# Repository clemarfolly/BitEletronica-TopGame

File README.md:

# A Bit Eletrônica e o Top Game

A Bit Eletrônica, fundada no Rio de Janeiro por Guilherme Ferramenta, criou o Top Game, o primeiro console de videogame brasileiro, lançado em dezembro de 1982. O console tinha um design diferenciado e era compatível com o sistema de TV PAL-M do Brasil. No entanto, ele utilizava um padrão próprio de cartuchos, devido ao receio de represálias da Atari. Apesar de boa aceitação inicial, a falta de capital e de publicidade, além da chegada de concorrentes maiores como a Philips e a Polyvox, levaram ao fim da Bit Eletrônica após a fabricação de cinco mil unidades. O Top Game tornou-se uma raridade entre colecionadores. Em 1984, a empresa lançou um adaptador para cartuchos do Atari 2600, mas isso não foi suficiente para salvar o negócio.

## Sobre essa reprodução

A reprodução do projeto foi realizada sem acesso físico à placa original, com base em fotos encontradas na internet. Para isso, utilizou-se os software Sprint Layout e o KiCad para desenhar o esquema e a placa de circuito impresso. A réplica ainda não foi produzida, e seu funcionamento não foi validado. Agradecemos às pessoas que disponibilizaram as fotos e o esquema original, permitindo que esse trabalho fosse possível.

### Datalhes das placas
A placa é dupla face, mesmo assim existem alguns jumpers. Esses jumpers foram roteados nas camadas internas de uma placa de 4 camadas. 

### Comparação com a placa original
Embora eu não tenha tido acesso físico à placa original, me esforcei para que a recriação ficasse o mais fiel possível. As imagens utilizadas como referência tinham baixa resolução e precisaram ter suas proporções ajustadas, além de estarem carregadas de componentes, o que complicou a reprodução das trilhas que passam por baixo deles.

## Créditos

### Recriação da Placa: 

Clemar Folly Jr.

https://x.com/clemarfolly/

### Fotos

Marcelo Savio

https://web.facebook.com/msavio.fb/posts/pfbid06LcW7Tc7TT6NtnfWvrCvcL87vY5sa6EqBfuqB7YxEga17TYGUfypFnMQQWhqyX86l

### Esquema

Alexandre Souza

http://www.tabalabs.com.br/esquemateca/$ESBREL/$pre-tratados/Top%20Game%20-%20Bit%20Eletronica.jpg

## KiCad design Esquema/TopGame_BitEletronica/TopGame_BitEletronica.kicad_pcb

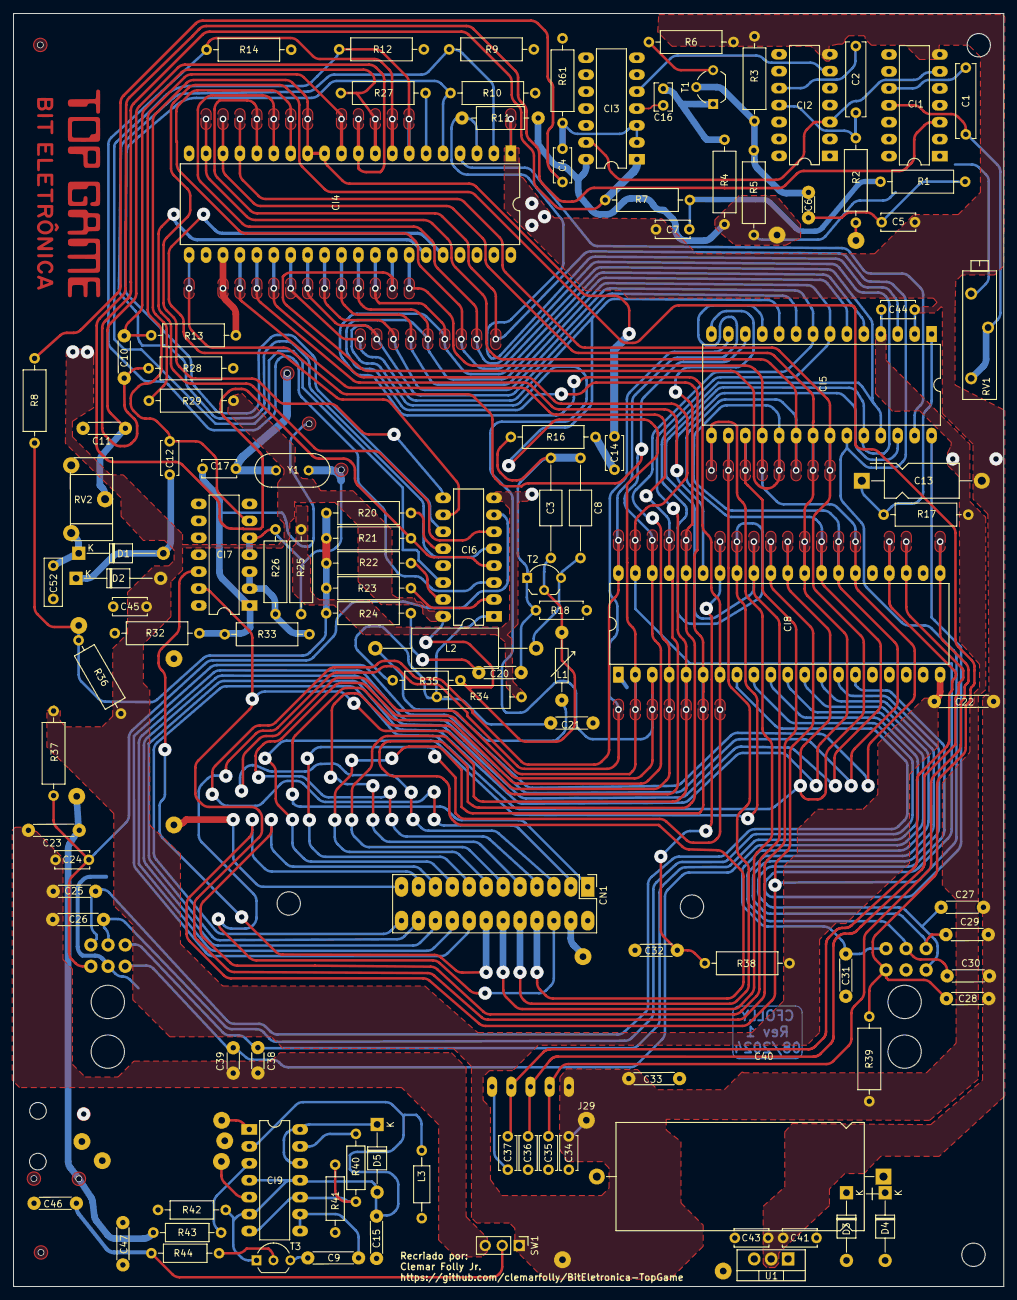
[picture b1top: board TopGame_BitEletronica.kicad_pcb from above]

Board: 4 copper layers, 148.5 x 190.9 mm, 144 parts (0 on the bottom side), 98 nets.

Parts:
C1, C2: C_Small; C_Rect_L11.0mm_W2.8mm_P10.00mm_MKT
C3, C8: 820p; C_Axial_L5.1mm_D3.1mm_P15.00mm_Horizontal
C4, C5, C7, C12, C17, C24, C34, C35, C36, C37, C41, C43, C45: C_Small; C_Disc_D5.0mm_W2.5mm_P5.00mm
C6, C38, C39: C_Small; C_Disc_D3.0mm_W1.6mm_P3.81mm
C9: 15p; C_Disc_D3.0mm_W1.6mm_P7.62mm
C10, C15, C20: 47p; C_Disc_D3.0mm_W1.6mm_P6.35mm
C11, C25, C27, C29, C30, C31, C46, C47: C_Small; C_Disc_D3.0mm_W1.6mm_P6.35mm
C13: 4.7uF/16V; CP_Axial_L11.0mm_D5.0mm_P18.00mm_Horizontal
C14: 100n; C_Disc_D5.0mm_W2.5mm_P5.00mm
C16: C_Small; C_Rect_L4.0mm_W2.5mm_P2.50mm
C21, C28: 220p; C_Disc_D3.0mm_W1.6mm_P6.35mm
C22: C_Mini; C_Disc_D3.0mm_W1.6mm_P8.89mm
C23, C26, C33: C_Small; C_Disc_D3.0mm_W1.6mm_P7.62mm
C32: C_Mini; C_Disc_D3.0mm_W1.6mm_P6.35mm
C40: CP_Small; CP_Axial_L37.0mm_D16.0mm_P43.00mm_Horizontal
C44: C_Mini; C_Disc_D5.0mm_W2.5mm_P5.00mm
C52: C_Small; C_Disc_D7.0mm_W2.5mm_P5.00mm
CI1, CI2: 74LS121; DIP-14_W7.62mm_LongPads
CI3: 4066; DIP-14_W7.62mm_LongPads
CI4: TIA; DIP-40_W15.24mm_LongPads
CI5: 6507; DIP-28_W15.24mm_LongPads
CI6: CD4050; DIP-16_W7.62mm_LongPads
CI7: 74LS04_SMALL; DIP-14_W7.62mm_LongPads
CI8: RIOT; DIP-40_W15.24mm_LongPads
CI9: LM3086; DIP-14_W7.62mm_LongPads
CN1: Conn_02x12_Counter_Clockwise; Atari2600_PCB_Edge_Connector_2x12_P2.54mm_5.08mm
D1, D2: D_ALT; D_T-1_P12.70mm_Horizontal
D3, D4, D5: D_ALT; D_T-1_P10.16mm_Horizontal
J3, J10: 6; Pin_2mm_Furo_1mm
J4, J11: 5; Pin_2mm_Furo_1mm
J6, J13: 7; Pin_2mm_Furo_1mm
J7, J14: 2; Pin_2mm_Furo_1mm
J8, J15: 3; Pin_2mm_Furo_1mm
J9, J16: 4; Pin_2mm_Furo_1mm
J17: +5V; Via Oval
J18: GND; Via Oval
J19: PB/C; Via Oval
J20: PAF; Via Oval
J21: SEL.; Via Oval
J22: +5V; Pad_3mm_furo_1mm
J23, J25, J26: GND; Pad_3mm_furo_1mm
J24: L4_3; Pad_3mm_furo_1mm
J27, J28, J29, J30, J31, J32, J33, J34: Pad_3mm_furo_1mm
L1: LTRIM; Indutor_Variavel_10.16mm
L2: L_Small; L_Axial_L12.8mm_D5.8mm_P24.13mm_Horizontal
L3: L; L_Axial_L5.3mm_D2.2mm_P10.16mm_Horizontal_Vishay_IM-1
R1, R2, R3, R4, R5, R6, R7, R8, R25, R26, R29, R32, R33, R36, R37, R38, R61: R; R_Axial_DIN0309_L9.0mm_D3.2mm_P12.70mm_Horizontal
R9, R10, R12, R14: 3k3; R_Axial_DIN0309_L9.0mm_D3.2mm_P12.70mm_Horizontal
R11: R; R_Axial_DIN0309_L9.0mm_D3.2mm_P11.43mm_Horizontal
R13, R24, R28: 1k; R_Axial_DIN0309_L9.0mm_D3.2mm_P12.70mm_Horizontal
R16: 18k; R_Axial_DIN0309_L9.0mm_D3.2mm_P12.70mm_Horizontal
R17, R21, R34, R39: 10k; R_Axial_DIN0309_L9.0mm_D3.2mm_P12.70mm_Horizontal
R18: 9k1; R_Axial_DIN0207_L6.3mm_D2.5mm_P7.62mm_Horizontal
R20: 24k; R_Axial_DIN0309_L9.0mm_D3.2mm_P12.70mm_Horizontal
R22: 12k; R_Axial_DIN0309_L9.0mm_D3.2mm_P12.70mm_Horizontal
R23: 47k; R_Axial_DIN0309_L9.0mm_D3.2mm_P12.70mm_Horizontal
R27: 680R; R_Axial_DIN0309_L9.0mm_D3.2mm_P12.70mm_Horizontal
R35: R; R_Axial_DIN0207_L6.3mm_D2.5mm_P10.16mm_Horizontal
R40: 1k5; R_Axial_DIN0207_L6.3mm_D2.5mm_P10.16mm_Horizontal
R41: 1k; R_Axial_DIN0207_L6.3mm_D2.5mm_P10.16mm_Horizontal
R42: 100R; R_Axial_DIN0207_L6.3mm_D2.5mm_P10.16mm_Horizontal
R43: 330R; R_Axial_DIN0207_L6.3mm_D2.5mm_P10.16mm_Horizontal
R44: 2k7; R_Axial_DIN0207_L6.3mm_D2.5mm_P10.16mm_Horizontal
RV1: R_POT_TRIM; Potentiometer_Bourns_3006P_Horizontal
RV2: R_POT_TRIM; Trimpot_14mm_Vertical
SW1: CHAVE CANAL; PinHeader_1x03_P2.54mm_Vertical
T1: NPN; TO-92_Wide
T2: MPS3563; TO-92_Invert_Wide
T3: MPS3906; TO-92_Inline_Wide
TP1, TP2: TestPoint; Pad_3mm_furo_1mm
U1: L7805; TO-220-3_Vertical
Y1: Crystal_Small; Crystal_HC49-U_Vertical

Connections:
+5V: C3.2, C22.1, C33.2, C34.1, C43.1, C44.1, C45.1, C47.1, CI1.14, CI2.14, CI3.14, CI4.20 (VCC), CI4.23 (CS1), CI5.4 (VCC), CI6.16, CI7.14 (VCC), CI8.20 (VDD), CN1.23, D2.2 (A), J17.1, J22.1, J28.1, J29.1, J30.1, J31.1, J32.1, J33.1, L1.1, R2.2, R4.2, R5.2, R9.1, R10.2, R11.1, R12.2, R13.2, R14.1, R17.2, R28.2, R29.1, R35.1, R36.2, R37.1, R38.1, R39.2, R42.1, RV1.3, SW1.1 (A), T2.2 (B), U1.3 (OUT)
+9V: C40.1, C41.1, D3.1 (K), D4.1 (K), U1.1 (IN)
D0: CI4.14 (D0), CI5.25 (D0), CI8.33 (D0), CN1.9
D1: CI4.15 (D1), CI5.24 (D1), CI8.32 (D1), CN1.10
GND: C5.2, C7.2, C11.2, C13.2, C21.1, C22.2, C23.2, C24.2, C25.2, C26.2, C27.2, C28.2, C29.2, C30.2, C31.2, C32.2, C33.1, C34.2, C35.2, C36.2, C37.2, C38.2, C39.2, C40.2, C41.2, C43.2, C44.2, C45.2, C46.2, C47.2, C52.2, CI1.7, CI2.7, CI3.7, CI4.1 (VSS), CI4.22 (CS2), CI5.2 (VSS), CI6.8, CI7.7 (GND), CI8.1 (VSS), CN1.12, CN1.24, J3.1, J10.1, J18.1, J25.1, J26.1, R3.1, R6.1, R18.1, R25.2, R32.1, R34.1, R41.2, R61.1, RV2.1, SW1.3 (C), U1.2 (GND)
unnamed: C4.2, R8.1
unnamed: C5.1, C6.1, R1.2
unnamed: C7.1, R1.1, R7.2
unnamed: C14.2, R16.2
unnamed: C17.1, Y1.1
unnamed: C17.2, CI7.1, R32.2, R33.1
unnamed: C20.2, R24.2
unnamed: CI1.3, CI6.4, R21.1
unnamed: CI1.6, CI2.3, CI3.13
unnamed: C1.2, CI1.10
unnamed: C1.1, CI1.11, RV1.1, RV1.2
unnamed: CI2.6, CI3.5
unnamed: C2.1, CI2.10
unnamed: C2.2, CI2.11, R2.1
unnamed: C10.2, CI3.1, R7.1, R28.1
unnamed: C4.1, CI3.2, CI3.3, R61.2
unnamed: C16.1, CI3.4
unnamed: CI4.32 (A0), CI5.5 (A0), CI8.7 (A0), CN1.8
unnamed: CI4.31 (A1), CI5.6 (A1), CI8.6 (A1), CN1.7
unnamed: CI4.30 (A2), CI5.7 (A2), CI8.5 (A2), CN1.6
unnamed: CI4.29 (A3), CI5.8 (A3), CI8.4 (A3), CN1.5
unnamed: CI4.28 (A4), CI5.9 (A4), CI8.3 (A4), CN1.4
unnamed: CI4.27 (A5), CI5.10 (A5), CI8.2 (A5), CN1.3
unnamed: C14.1, CI4.12 (AUD0), CI4.13 (AUD1), R29.2
unnamed: CI4.6 (BLK), R27.1
unnamed: C10.1, CI4.9 (COL), R13.1, R27.2
unnamed: CI4.24 (CS0), CI5.17 (A12), CI7.13, CI8.37 (CS2)
unnamed: CI4.21 (CS3), CI5.12 (A7), CI8.38 (CS1), CN1.1
unnamed: CI4.16 (D2), CI5.23 (D2), CI8.31 (D2), CN1.11
unnamed: CI4.17 (D3), CI5.22 (D3), CI8.30 (D3), CN1.13
unnamed: CI4.18 (D4), CI5.21 (D4), CI8.29 (D4), CN1.14
unnamed: CI4.19 (D5), CI5.20 (D5), CI8.28 (D5), CN1.15
unnamed: CI4.34 (D6), CI5.18 (D7), CI8.26 (D7), CN1.17
unnamed: CI4.33 (D7), CI5.19 (D6), CI8.27 (D6), CN1.16
unnamed: C11.1, CI4.10 (DEL), RV2.2
unnamed: CI4.36 (I4), CI6.10
unnamed: CI4.35 (I5), CI6.6
unnamed: CI4.8 (LUM0), CI6.3, R14.2
unnamed: CI4.5 (LUM1), CI6.11, R10.1
unnamed: CI4.7 (LUM2), CI6.14, R12.1
unnamed: C12.2, CI4.11 (OSC), CI7.6
unnamed: CI4.4 (PHI0), CI5.27 (PHI0)
unnamed: CI4.26 (PHI2), CI5.28 (PHI2), CI8.39 (PHI2)
unnamed: CI4.3 (RDY), CI5.3 (RDY), R11.2
unnamed: CI4.25 (R/~W), CI5.26 (R/~W), CI8.35 (R/~W)
unnamed: CI4.2 (SYNC), CI6.5, R9.2
unnamed: CI5.11 (A6), CI8.40 (A6), CN1.2
unnamed: CI5.13 (A8), CN1.22
unnamed: CI5.14 (A9), CI8.36 (RS), CN1.21
unnamed: CI5.15 (A10), CN1.19
unnamed: CI5.16 (A11), CN1.20
unnamed: C13.1, CI5.1 (RES), R17.1
unnamed: C21.2, CI6.1, R34.2, R35.2
unnamed: CI6.2, R23.1
unnamed: C24.1, CI6.7, J11.1, R37.2
unnamed: C28.1, CI6.9, J4.1, R39.1
unnamed: CI6.12, R20.1
unnamed: CI6.15, R22.1
unnamed: CI7.2, CI7.3, R26.1, R33.2
unnamed: CI7.4, CI7.5, R25.1, R26.2, Y1.2
unnamed: C25.1, CI8.8 (PA0), J16.1
unnamed: C26.1, CI8.9 (PA1), J15.1
unnamed: C38.1, CI8.10 (PA2), J14.1
unnamed: C39.1, CI8.11 (PA3), J13.1
unnamed: C31.1, CI8.12 (PA4), J9.1
unnamed: C30.1, CI8.13 (PA5), J8.1
unnamed: C29.1, CI8.14 (PA6), J7.1
unnamed: C27.1, CI8.15 (PA7), J6.1
unnamed: C37.1, CI8.24 (PB0), J20.1
unnamed: C36.1, CI8.23 (PB1), J21.1
unnamed: C35.1, CI8.21 (PB3), J19.1
unnamed: C32.1, CI8.34 (RES), R38.2
unnamed: CI9.1, J23.1
unnamed: CI9.3, R43.2
unnamed: CI9.5, J24.1
unnamed: C9.2, C15.2, CI9.8, CI9.9, L3.1
unnamed: CI9.7, CI9.10, R40.2, R41.1
unnamed: C15.1, CI9.2, CI9.4, CI9.6, CI9.11, D5.2 (A), L3.2, R42.2, T3.1 (E)
unnamed: CI9.12, CI9.14, D5.1 (K)
unnamed: CI9.13, R40.1
unnamed: CI7.12, CN1.18
unnamed: C12.1, D1.2 (A), D2.1 (K)
unnamed: C52.1, D1.1 (K), RV2.3
unnamed: C23.1, J27.1, J34.1, R8.2, R20.2, R21.2, R22.2, R23.2, R24.1, R36.1, R43.1
unnamed: L1.2, L2.2
unnamed: C46.1, R44.1, SW1.2 (B)
unnamed: C6.2, R3.2, R5.1, T1.2 (B)
unnamed: C16.2, R4.1, T1.1 (C)
unnamed: R6.2, T1.3 (E)
unnamed: C8.2, L2.1, T2.3 (C)
unnamed: C3.1, C8.1, C20.1, R16.1, R18.2, T2.1 (E)
unnamed: R44.2, T3.2 (B)
unnamed: C9.1, T3.3 (C)

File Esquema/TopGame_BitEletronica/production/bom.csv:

Designator,Footprint,Quantity,Value,LCSC Part #
"C1, C2",C_Rect_L11.0mm_W2.8mm_P10.00mm_MKT,2,C_Small,
"C10, C15, C20",C_Disc_D3.0mm_W1.6mm_P6.35mm,3,47p,
"C11, C25, C27, C29, C30, C31, C46, C47",C_Disc_D3.0mm_W1.6mm_P6.35mm,8,C_Small,
"C12, C17, C24, C34, C35, C36, C37, C4, C41, C43, C45, C5, C7",C_Disc_D5.0mm_W2.5mm_P5.00mm,13,C_Small,
C13,CP_Axial_L11.0mm_D5.0mm_P18.00mm_Horizontal,1,4.7uF/16V,
C14,C_Disc_D5.0mm_W2.5mm_P5.00mm,1,100n,
C16,C_Rect_L4.0mm_W2.5mm_P2.50mm,1,C_Small,
"C21, C28",C_Disc_D3.0mm_W1.6mm_P6.35mm,2,220p,
C22,C_Disc_D3.0mm_W1.6mm_P8.89mm,1,C_Mini,
"C23, C26, C33",C_Disc_D3.0mm_W1.6mm_P7.62mm,3,C_Small,
"C3, C8",C_Axial_L5.1mm_D3.1mm_P15.00mm_Horizontal,2,820p,
C32,C_Disc_D3.0mm_W1.6mm_P6.35mm,1,C_Mini,
"C38, C39, C6",C_Disc_D3.0mm_W1.6mm_P3.81mm,3,C_Small,
C40,CP_Axial_L37.0mm_D16.0mm_P43.00mm_Horizontal,1,CP_Small,
C44,C_Disc_D5.0mm_W2.5mm_P5.00mm,1,C_Mini,
C52,C_Disc_D7.0mm_W2.5mm_P5.00mm,1,C_Small,
C9,C_Disc_D3.0mm_W1.6mm_P7.62mm,1,15p,
"CI1, CI2",DIP-14_W7.62mm_LongPads,2,74LS121,
CI3,DIP-14_W7.62mm_LongPads,1,4066,
CI4,DIP-40_W15.24mm_LongPads,1,TIA,
CI5,DIP-28_W15.24mm_LongPads,1,6507,
CI6,DIP-16_W7.62mm_LongPads,1,CD4050,
CI7,DIP-14_W7.62mm_LongPads,1,74LS04_SMALL,
CI8,DIP-40_W15.24mm_LongPads,1,RIOT,
CI9,DIP-14_W7.62mm_LongPads,1,LM3086,
CN1,Atari2600_PCB_Edge_Connector_2x12_P2.54mm_5.08mm,1,Conn_02x12_Counter_Clockwise,
"D1, D2",D_T-1_P12.70mm_Horizontal,2,D_ALT,
"D3, D4, D5",D_T-1_P10.16mm_Horizontal,3,D_ALT,
"J10, J3",Pin_2mm_Furo_1mm,2,6,
"J11, J4",Pin_2mm_Furo_1mm,2,5,
"J13, J6",Pin_2mm_Furo_1mm,2,7,
"J14, J7",Pin_2mm_Furo_1mm,2,2,
"J15, J8",Pin_2mm_Furo_1mm,2,3,
"J16, J9",Pin_2mm_Furo_1mm,2,4,
J17,Via Oval,1,+5V,
J18,Via Oval,1,GND,
J19,Via Oval,1,PB/C,
J20,Via Oval,1,PAF,
J21,Via Oval,1,SEL.,
J22,Pad_3mm_furo_1mm,1,+5V,
"J23, J25, J26",Pad_3mm_furo_1mm,3,GND,
J24,Pad_3mm_furo_1mm,1,L4_3,
"J27, J28, J29, J30, J31, J32, J33, J34",Pad_3mm_furo_1mm,8,~,
L1,Indutor_Variavel_10.16mm,1,LTRIM,
L2,L_Axial_L12.8mm_D5.8mm_P24.13mm_Horizontal,1,L_Small,
L3,L_Axial_L5.3mm_D2.2mm_P10.16mm_Horizontal_Vishay_IM-1,1,L,
"R1, R2, R25, R26, R29, R3, R32, R33, R36, R37, R38, R4, R5, R6, R61, R7, R8",R_Axial_DIN0309_L9.0mm_D3.2mm_P12.70mm_Horizontal,17,R,
"R10, R12, R14, R9",R_Axial_DIN0309_L9.0mm_D3.2mm_P12.70mm_Horizontal,4,3k3,
R11,R_Axial_DIN0309_L9.0mm_D3.2mm_P11.43mm_Horizontal,1,R,
"R13, R24, R28",R_Axial_DIN0309_L9.0mm_D3.2mm_P12.70mm_Horizontal,3,1k,
R16,R_Axial_DIN0309_L9.0mm_D3.2mm_P12.70mm_Horizontal,1,18k,
"R17, R21, R34, R39",R_Axial_DIN0309_L9.0mm_D3.2mm_P12.70mm_Horizontal,4,10k,
R18,R_Axial_DIN0207_L6.3mm_D2.5mm_P7.62mm_Horizontal,1,9k1,
R20,R_Axial_DIN0309_L9.0mm_D3.2mm_P12.70mm_Horizontal,1,24k,
R22,R_Axial_DIN0309_L9.0mm_D3.2mm_P12.70mm_Horizontal,1,12k,
R23,R_Axial_DIN0309_L9.0mm_D3.2mm_P12.70mm_Horizontal,1,47k,
R27,R_Axial_DIN0309_L9.0mm_D3.2mm_P12.70mm_Horizontal,1,680R,
R35,R_Axial_DIN0207_L6.3mm_D2.5mm_P10.16mm_Horizontal,1,R,
R40,R_Axial_DIN0207_L6.3mm_D2.5mm_P10.16mm_Horizontal,1,1k5,
R41,R_Axial_DIN0207_L6.3mm_D2.5mm_P10.16mm_Horizontal,1,1k,
R42,R_Axial_DIN0207_L6.3mm_D2.5mm_P10.16mm_Horizontal,1,100R,
R43,R_Axial_DIN0207_L6.3mm_D2.5mm_P10.16mm_Horizontal,1,330R,
R44,R_Axial_DIN0207_L6.3mm_D2.5mm_P10.16mm_Horizontal,1,2k7,
RV1,Potentiometer_Bourns_3006P_Horizontal,1,R_POT_TRIM,
RV2,Trimpot_14mm_Vertical,1,R_POT_TRIM,
SW1,PinHeader_1x03_P2.54mm_Vertical,1,CHAVE CANAL,
T1,TO-92_Wide,1,NPN,
T2,TO-92_Invert_Wide,1,MPS3563,
T3,TO-92_Inline_Wide,1,MPS3906,
"TP1, TP2",Pad_3mm_furo_1mm,2,TestPoint,
U1,TO-220-3_Vertical,1,L7805,
Y1,Crystal_HC49-U_Vertical,1,Crystal_Small,

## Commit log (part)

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2024-08-29 Revisão 1 da placa finalizada.
2026-03-26 Update README.md
    Correção no nome do fundador da Bit Eletronica
